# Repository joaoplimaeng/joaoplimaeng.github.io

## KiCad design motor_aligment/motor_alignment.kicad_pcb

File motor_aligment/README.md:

# Motor Cap Alignment — Sensor Indutivo com ESP32

Ferramenta de medição de deflexão da tampa do motor usando sensor indutivo analógico, ADC ADS1115, LCD I2C 1602 e botão discreto.

---

## Componentes

| Componente | Modelo |
|---|---|
| Microcontrolador | ESP32 NodeMCU-32 (30 pinos) |
| Sensor indutivo | METALTEX I18-8-ANV (0–10V, range 8mm) |
| ADC | ADS1115 (16-bit, I2C) |
| Display | LCD 1602 I2C (módulo PCF8574, endereço 0x27) |
| Botão | Botão tátil discreto (NO — normalmente aberto) |
| Fonte | 24V + LM2596 step-down para 5V |
| Resistores | 2× 10kΩ (divisor de tensão do sensor) |

---

## Topologia de Ligação

```
┌──────────────────────────────────────────────────────────────────────┐
│                            FONTE 24V                                 │
└──────┬───────────────────────────────────────┬─────────────────────-─┘
       │                                       │
       ▼                                       ▼
┌─────────────┐                      ┌──────────────────┐
│  METALTEX   │                      │  LM2596 Step-Down│
│ I18-8-ANV   │                      │    24V → 5V      │
│ OUT (0–10V) │                      └────────┬─────────┘
└──────┬──────┘                               │ 5V
       │                     ┌────────────────┼──────────────┬──────────────┐
       ▼                     │                │              │              │
    R1=10kΩ                  ▼                ▼              ▼              ▼
       │              ┌──────────┐     ┌──────────┐  ┌────────────┐  ┌──────────┐
    [ADS1115 A0]      │  ESP32   │     │ ADS1115  │  │ LCD 1602   │  │  Botão   │
       │              │NodeMCU-32│     │  (I2C)   │  │   (I2C)    │  │Discreto  │
    R2=10kΩ           └──────────┘     └──────────┘  └────────────┘  └──────────┘
       │
      GND
```

---

## Divisor de Tensão do Sensor (obrigatório)

O sensor entrega até **10V**, o ADS1115 suporta no máximo ~6.1V. O divisor 3:1 reduz para 0–3.33V:

```
Sensor OUT ──── R1 (10kΩ) ──┬──── ADS1115 A0
                             │
                          R2 (5kΩ)
                             │
                            GND
```

| Tensão do sensor | Tensão no ADS1115 | Distância |
|---|---|---|
| 0V | 0V | 0.00 mm |
| 5V | 1.67V | 4.00 mm |
| 10V | 3.33V | 8.00 mm |

---

## Barramento I2C → ESP32

O LCD e o ADS1115 **compartilham o mesmo barramento I2C**:

| Sinal | ESP32 GPIO |
|---|---|
| SDA | GPIO 21 |
| SCL | GPIO 22 |

| Dispositivo | Endereço I2C |
|---|---|
| ADS1115 | 0x48 (padrão) |
| LCD PCF8574 | 0x27 (típico) — tente 0x3F se não funcionar |

---

## Conexões ADS1115

| ADS1115 | ESP32 |
|---|---|
| SDA | GPIO 21 |
| SCL | GPIO 22 |
| VCC | 5V |
| GND | GND |
| A0 | Saída do divisor de tensão |

---

## Conexões LCD 1602 I2C

| LCD I2C (PCF8574) | ESP32 |
|---|---|
| SDA | GPIO 21 |
| SCL | GPIO 22 |
| VCC | 5V |
| GND | GND |

> O backlight é controlado pelo próprio módulo PCF8574 via `lcd.backlight()` no código.

---

## Conexão do Botão Discreto

O botão é do tipo **NO (normalmente aberto)**. Um terminal vai ao GPIO e o outro ao GND. O pull-up interno do ESP32 mantém o pino em HIGH; pressionar o botão força LOW.

```
GPIO 32 ──── [ BTN ] ──── GND
              (NO)
```

| Sinal | ESP32 GPIO |
|---|---|
| Botão | GPIO 32 |
| GND | GND |

> Não é necessário resistor externo — o código usa `INPUT_PULLUP`.

---

## Como Compilar e Gravar

### Opção A — Arduino IDE (GUI)

#### 1. Instalar o Arduino IDE

```bash
# Baixe o AppImage em https://arduino.cc/en/software e torne executável:
chmod +x arduino-ide_*.AppImage
./arduino-ide_*.AppImage
```

#### 2. Permissão de porta serial (Linux)

```bash
sudo usermod -aG dialout $USER
# Faça logout e login novamente para aplicar
```

#### 3. Adicionar suporte ao ESP32

1. Abra *File → Preferences*
2. No campo **Additional Boards Manager URLs**, cole:
   ```
   https://raw.githubusercontent.com/espressif/arduino-esp32/gh-pages/package_esp32_index.json
   ```
3. Clique em OK
4. Vá em *Tools → Board → Boards Manager*
5. Busque `esp32`, selecione o pacote da **Espressif Systems** e clique em **Install**

#### 4. Instalar as bibliotecas

Vá em *Tools → Manage Libraries* e instale:

| Biblioteca | Autor |
|---|---|
| `Adafruit ADS1X15` | Adafruit |
| `LiquidCrystal_I2C` | Frank de Brabander |

#### 5. Configurar e gravar

1. *Tools → Board → ESP32 Arduino* → `NodeMCU-32S` (ou `ESP32 Dev Module`)
2. *Tools → Port* → `/dev/ttyUSB0` ou `/dev/ttyACM0`
3. Clique em **Upload** (→)

> Se o upload travar, segure o botão **BOOT** do ESP32 enquanto o upload inicia.

---

### Opção B — arduino-cli (linha de comando)

Mais rápido para quem prefere terminal.

#### 1. Instalar o arduino-cli

```bash
curl -fsSL https://raw.githubusercontent.com/arduino/arduino-cli/master/install.sh | sh
sudo mv bin/arduino-cli /usr/local/bin/
```

#### 2. Permissão de porta serial

```bash
sudo usermod -aG dialout $USER
# Faça logout e login novamente para aplicar
```

#### 3. Configurar o arduino-cli

```bash
arduino-cli config init
arduino-cli config add board_manager.additional_urls \
  https://raw.githubusercontent.com/espressif/arduino-esp32/gh-pages/package_esp32_index.json
arduino-cli core update-index
arduino-cli core install esp32:esp32
```

#### 4. Instalar as bibliotecas

```bash
arduino-cli lib install "Adafruit ADS1X15"
arduino-cli lib install "LiquidCrystal I2C"
```

#### 5. Compilar

```bash
arduino-cli compile \
  --fqbn esp32:esp32:nodemcu-32s \
  motor_alignment.ino
```

#### 6. Identificar a porta

```bash
arduino-cli board list
# Exemplo de saída:
# /dev/ttyUSB0   Serial Port (USB)   CP2102 ...
```

#### 7. Gravar

```bash
arduino-cli upload \
  --fqbn esp32:esp32:nodemcu-32s \
  --port /dev/ttyUSB0 \
  motor_alignment.ino
```

> Se preferir compilar e gravar em um único comando:
> ```bash
> arduino-cli compile --fqbn esp32:esp32:nodemcu-32s motor_alignment.ino && \
> arduino-cli upload  --fqbn esp32:esp32:nodemcu-32s --port /dev/ttyUSB0 motor_alignment.ino
> ```

#### 8. Monitor serial (opcional)

```bash
arduino-cli monitor --port /dev/ttyUSB0 --config baudrate=115200
```

---

## Solução de Problemas

| Sintoma | Causa provável | Solução |
|---|---|---|
| LCD não acende | Endereço I2C errado | Troque `0x27` por `0x3F` no define `LCD_I2C_ADDR` |
| LCD acende mas sem texto | Contraste do potenciômetro do módulo PCF8574 | Ajuste o trimpot na parte traseira do módulo |
| Botão não responde | Conexão GND ou GPIO errada | Verifique se um terminal vai ao GPIO 32 e o outro ao GND |
| ADS1115 não encontrado | Endereço ou fiação I2C | Confirme SDA→GPIO21, SCL→GPIO22 e alimentação 5V |

---

## Como Usar

1. Ligue o equipamento — display mostra `Pressione BTN`
2. Posicione o sensor na referência (posição zero)
3. Pressione o **botão discreto**
4. O sistema coleta amostras por **10 segundos** com countdown e calcula a média como referência
5. Display passa a mostrar a distância e o status:

```
Dist: X.XX mm
d=+0.12mm  OK        ← variação ≤ 1mm
```
```
Dist: X.XX mm
d=-1.47mm NOK        ← variação > 1mm
```

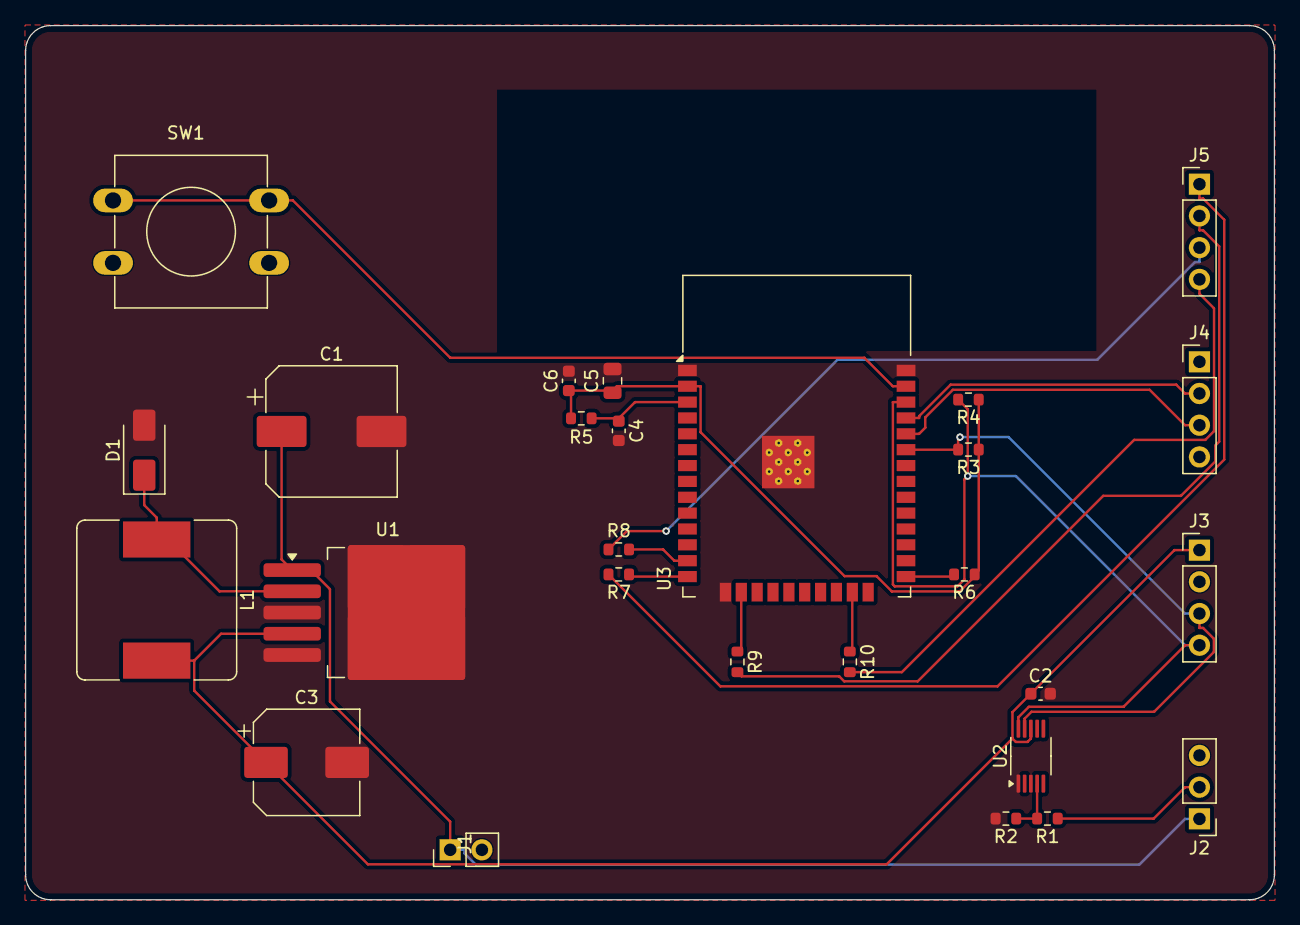
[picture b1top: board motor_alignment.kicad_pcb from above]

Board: 2 copper layers, 100.0 x 70.0 mm, 27 parts (0 on the bottom side), 22 nets.

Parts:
C1: 680u; CP_Elec_10x10
C2: 100n; C_0603_1608Metric
C3: 220u; CP_Elec_8x10
C4: 1uF; C_0603_1608Metric
C5: 10uF; C_0805_2012Metric
C6: 100nF; C_0603_1608Metric
D1: 1N5824; D_SMA
J1: PWR_24V_IN; PinHeader_1x02_P2.54mm_Vertical
J2: SENSOR_IN; PinHeader_1x03_P2.54mm_Vertical
J3: LCD_I2C; PinHeader_1x04_P2.54mm_Vertical
J4: UART_DOWNLOAD; PinHeader_1x04_P2.54mm_Vertical
J5: JTAG; PinHeader_1x04_P2.54mm_Vertical
L1: 33u; L_Bourns_SRR1260
R1, R5, R6: 10k; R_0603_1608Metric
R2: 5k; R_0603_1608Metric
R3, R4: 4k7; R_0603_1608Metric
R7, R8, R9, R10: 100R; R_0603_1608Metric
SW1: BTN; SW_PUSH-12mm
U1: LM2596S-5; TO-263-5_TabPin3
U2: ADS1115; VSSOP-10_3x3mm_P0.5mm
U3: ESP32-WROOM-32

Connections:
/+3.3V: C5.1, C6.1, R3.1, R4.1, R5.1, R6.1, U3.2 (VDD)
/+5V: C2.1, C3.1, J3.1, L1.2, U1.4 (FB), U2.8 (VDD)
/+24V: C1.1, J1.1, J2.1, U1.1 (VIN)
/BTN: SW1.1, U3.37 (IO23)
/ESP32_EN: C4.1, R5.2, U3.3 (EN)
/JTAG_TCK: J5.2, R9.2
/JTAG_TDI: J5.1, R7.2
/JTAG_TDO: J5.4, R10.2
/JTAG_TMS: J5.3, R8.2
/SCL: J3.4, R4.2, U2.10 (SCL), U3.36 (IO22)
/SDA: J3.3, R3.2, U2.9 (SDA), U3.33 (IO21)
/SENSOR_DIV: R1.2, R2.1, U2.4 (AIN0)
/SENSOR_OUT: J2.2, R1.1
/UART_RX: J4.3, U3.34 (RXD0/IO3)
/UART_TX: J4.2, U3.35 (TXD0/IO1)
GND: C1.2, C2.2, C3.2, C4.2, C5.2, C6.2, D1.2 (A), J1.2, J2.3, J3.2, J4.4, R2.2, SW1.2, U1.3 (GND), U1.5 (~ON/OFF), U2.1 (ADDR), U2.3 (GND), U3.1 (GND), U3.15 (GND), U3.38 (GND), U3.39 (GND)
unnamed: D1.1 (K), L1.1, U1.2 (OUT)
unnamed: R6.2, U3.25 (IO0)
unnamed: R7.1, U3.14 (IO12)
unnamed: R9.1, U3.16 (IO13)
unnamed: R8.1, U3.13 (IO14)
unnamed: R10.1, U3.23 (IO15)

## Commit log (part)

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2025-11-11 Rename grafico_guinchos.html to grafico_guinchos_11_11_25.html
2026-03-17 Add immobilizing issues WBR chart
2026-04-23 thermal_model
2026-06-03 gerador de certificado
2026-06-03 atualização do certificado
2026-06-03 Add motor alignment ESP32 project
2026-06-03 Move files into motor_aligment folder
